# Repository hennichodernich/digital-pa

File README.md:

# digital-pa
A digital mode power amplifier for 160-10m

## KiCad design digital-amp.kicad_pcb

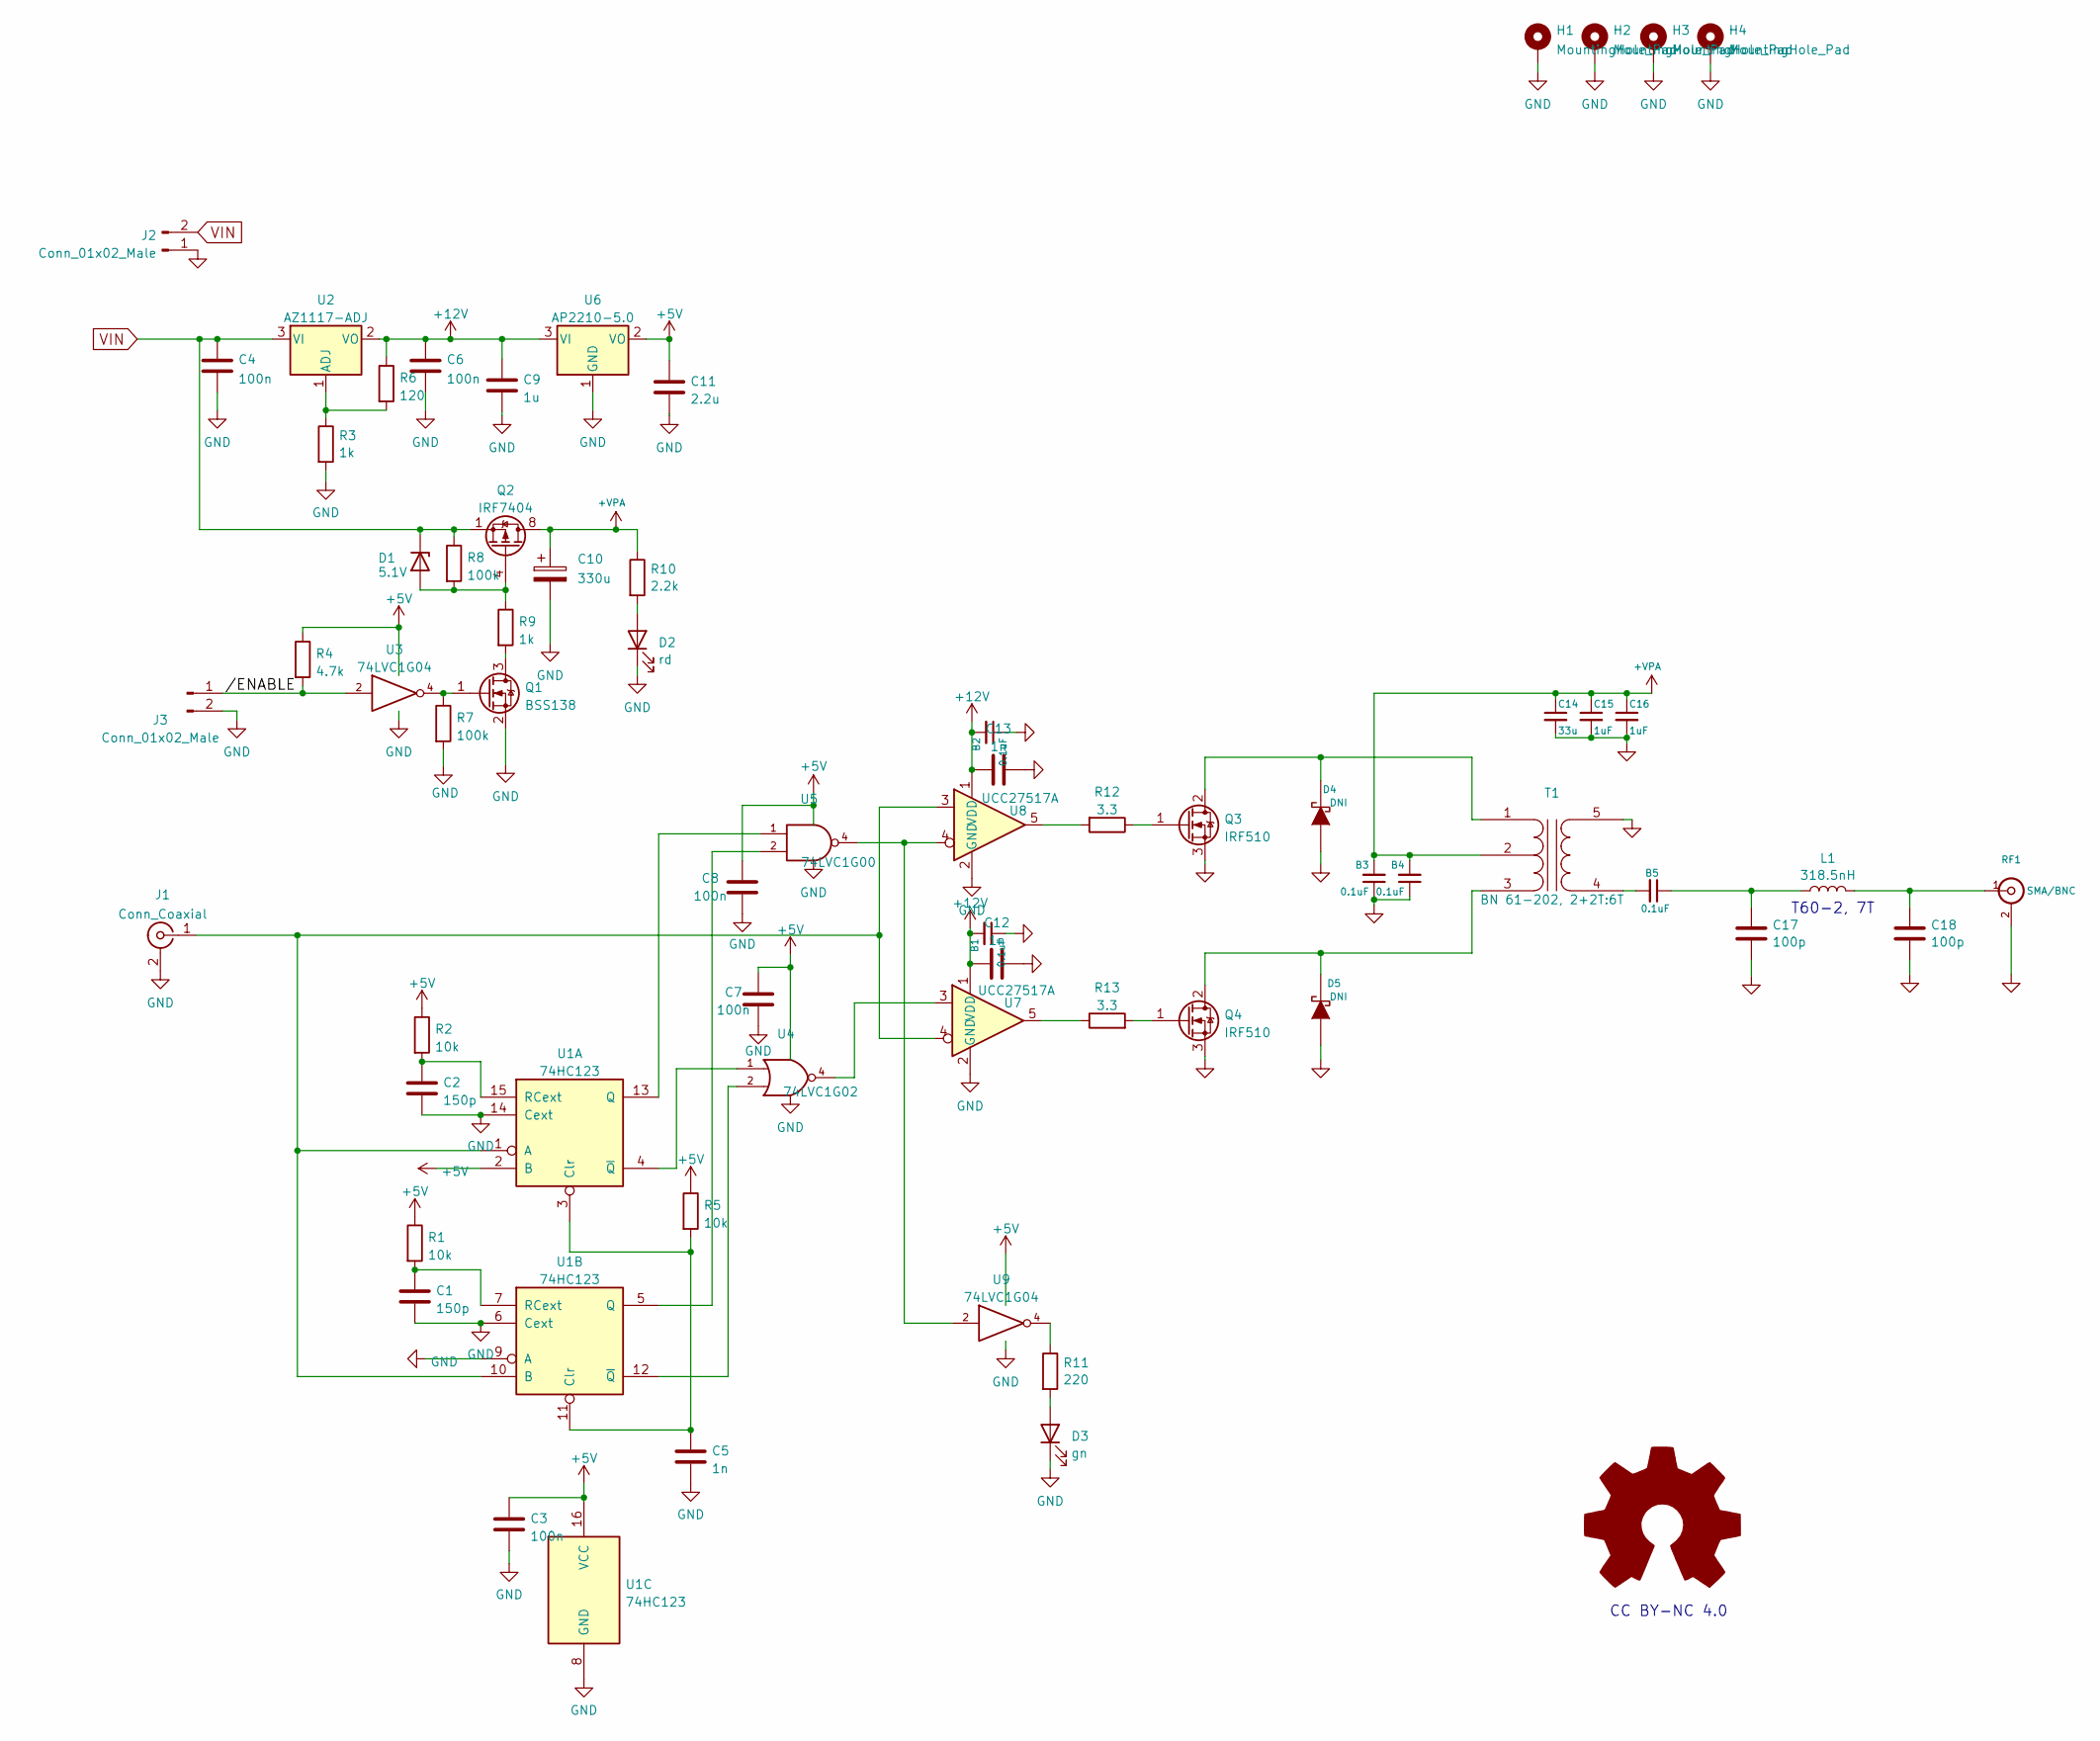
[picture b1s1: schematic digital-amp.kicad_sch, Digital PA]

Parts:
B1, B2, B3, B4, B5: 0.1uF; C_0603_1608Metric
C1, C2: 150p; C_0603_1608Metric
C3, C7, C8: 100n; C_0402_1005Metric
C4, C6: 100n; C_0603_1608Metric
C5: 1n; C_0603_1608Metric
C9: 1u; C_0805_2012Metric
C10: 330u; CP_Radial_D10.0mm_P5.00mm
C11: 2.2u; C_0805_2012Metric
C12, C13: 1n; C_0402_1005Metric
C14: 33u; C_2220_5650Metric
C15, C16: 1uF; C_0805_2012Metric
C17, C18: 100p; C_1206_3216Metric
D1: 5.1V; D_MiniMELF
D2: rd; LED_0603_1608Metric
D3: gn; LED_0603_1608Metric
D4, D5: np; D_SOD-323F
H1, H2, H3, H4: MountingHole_Pad; MountingHole_3.2mm_M3_DIN965_Pad
J1: Conn_Coaxial; SMA_Amphenol_901-144_Vertical
J2: Conn_01x02_Male; PhoenixContact_MSTBA_2,5_2-G-5,08_1x02_P5.08mm_Horizontal
J3: Conn_01x02_Male; PinHeader_1x02_P2.54mm_Vertical
L1: 318.5nH; L_Toroid_Vertical_L21.6mm_W8.4mm_P8.38mm_Pulse_G
Q1: BSS138; SOT-23
Q2: IRF7404; SOIC-8_3.9x4.9mm_P1.27mm
Q3, Q4: IRF510; TO-263-3_TabPin2
R1, R2, R5: 10k; R_0603_1608Metric
R3, R9: 1k; R_0603_1608Metric
R4: 4.7k; R_0603_1608Metric
R6: 120; R_0603_1608Metric
R7, R8: 100k; R_0603_1608Metric
R10: 2.2k; R_0603_1608Metric
R11: 220; R_0603_1608Metric
R12, R13: 3.3; R_0402_1005Metric
RF1: SMA/BNC; SMA_Amphenol_901-144_Vertical
T1: BN 61-202, 2+2T:6T; BN202V
U1: 74HC123; TSSOP-16_4.4x5mm_P0.65mm
U2: AZ1117-ADJ; SOT-223-3_TabPin2
U3, U9: 74LVC1G04; TSOT-23-5
U4: 74LVC1G02; TSOT-23-5
U5: 74LVC1G00; TSOT-23-5
U6: AP2210-5.0; SOT-23
U7, U8: UCC27517A; SOT-23-5

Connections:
+5V: C3.1, C7.1, C8.1, C11.1, R1.1, R2.1, R4.1, R5.1, U1.2 (B), U1.16 (VCC), U3.5 (VCC), U4.5 (VCC), U5.5 (VCC), U6.2 (VO), U9.5 (VCC)
+12V: B1.2, B2.2, C6.1, C9.1, C12.1, C13.1, R6.1, U2.2 (VO), U6.3 (VI), U7.1 (VDD), U8.1 (VDD)
+VPA: B3.2, B4.2, C10.1, C14.1, C15.1, C16.1, Q2.5 (D), Q2.6 (D), Q2.7 (D), Q2.8 (D), R10.1, T1.2 (PM)
//ENABLE: J3.1, R4.2, U3.2
GND: B1.1, B2.1, B3.1, B4.1, C1.2, C2.2, C3.2, C4.2, C5.2, C6.2, C7.2, C8.2, C9.2, C10.2, C11.2, C12.2, C13.2, C14.2, C15.2, C16.2, C17.2, C18.2, D2.1 (K), D3.1 (K), D4.2 (A), D5.2 (A), H1.1, H2.1, H3.1, H4.1, J1.2 (Ext), J2.1, J3.2, Q1.2 (S), Q3.3 (S), Q4.3 (S), R3.2, R7.2, RF1.2 (Ext), T1.5 (S1), U1.6 (Cext), U1.8 (GND), U1.9 (A), U1.14 (Cext), U3.3 (GND), U4.3 (GND), U5.3 (GND), U6.1 (GND), U7.2 (GND), U8.2 (GND), U9.3 (GND)
unnamed: B5.1, C17.1, L1.1
unnamed: D1.2 (A), Q2.4 (G), R8.2, R9.1
unnamed: D2.2 (A), R10.2
unnamed: D3.2 (A), R11.2
unnamed: D4.1 (K), Q3.2 (D), T1.1 (PR1)
unnamed: D5.1 (K), Q4.2 (D), T1.3 (PR2)
unnamed: J1.1 (In), U1.1 (A), U1.10 (B), U7.4, U8.3
unnamed: Q1.3 (D), R9.2
unnamed: Q1.1 (G), R7.1, U3.4
unnamed: Q3.1 (G), R12.1
unnamed: Q4.1 (G), R13.2
unnamed: R11.1, U9.4
unnamed: R12.2, U8.5
unnamed: R13.1, U7.5
unnamed: C18.1, L1.2, RF1.1 (In)
unnamed: B5.2, T1.4 (S2)
unnamed: C5.1, R5.2, U1.3 (Clr), U1.11 (Clr)
unnamed: U1.13 (Q), U5.1
unnamed: C2.1, R2.2, U1.15 (RCext)
unnamed: U1.4 (~Q), U4.1
unnamed: U1.5 (Q), U5.2
unnamed: C1.1, R1.2, U1.7 (RCext)
unnamed: U1.12 (~Q), U4.2
unnamed: R3.1, R6.2, U2.1 (ADJ)
unnamed: U4.4, U7.3
unnamed: U5.4, U8.4, U9.2
VIN: C4.1, D1.1 (K), J2.2, Q2.1 (S), Q2.2 (S), Q2.3 (S), R8.1, U2.3 (VI)

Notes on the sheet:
CC BY-NC 4.0
T60-2, 7T

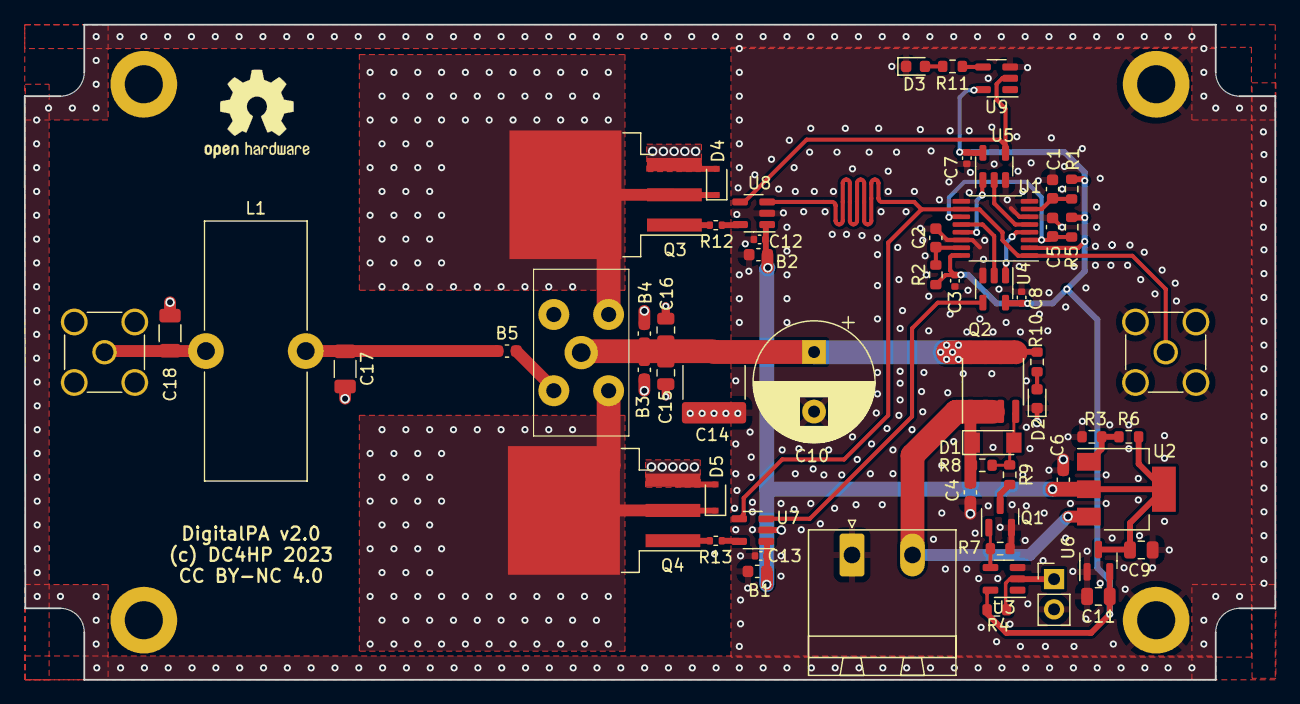
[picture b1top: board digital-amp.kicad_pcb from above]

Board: 2 copper layers, 105.0 x 55.0 mm, 64 parts (0 on the bottom side), 32 nets.

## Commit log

2023-09-10 Initial commit.
2023-09-10 Added a bit of information.
2023-10-26 Add slide set

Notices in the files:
digital-amp.kicad_sch:
Licensed under CC BY-NC 4.0
https://creativecommons.org/licenses/by-nc/4.0
